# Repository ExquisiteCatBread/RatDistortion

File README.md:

# RatDistortion
Guitar pedal based on Proco RAT

See "Distortion pedal project documentation.pdf"

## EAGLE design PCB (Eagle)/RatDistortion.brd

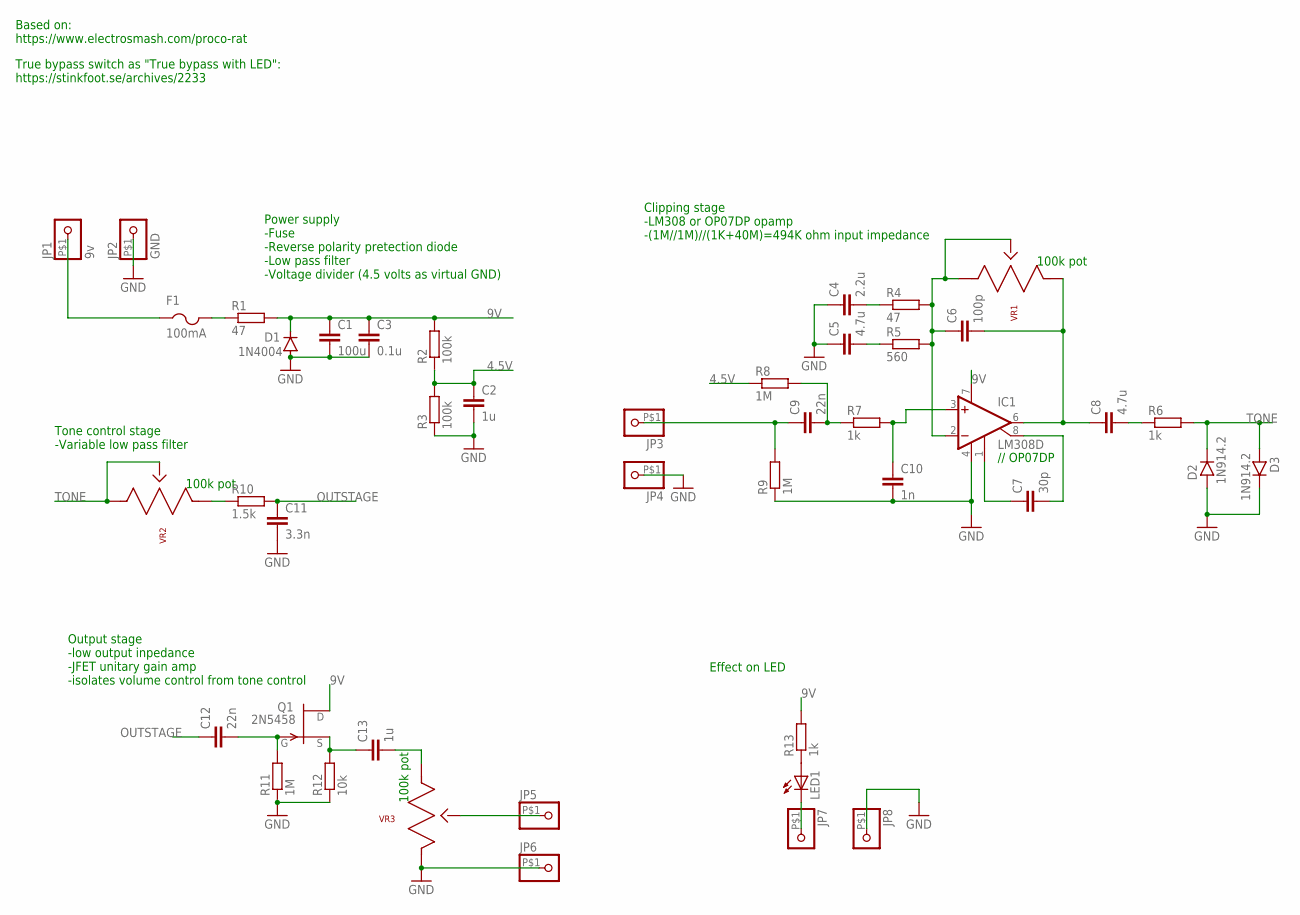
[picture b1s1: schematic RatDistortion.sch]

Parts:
C1: 100u; C1206
C2, C13: 1u; C1206
C3: 0.1u; C0603
C4: 2.2u; C1206
C5, C8: 4.7u; C1206
C6: 100p; C0603
C7: 30p; C0603
C9, C12: 22n; C0603
C10: 1n; C0603
C11: 3.3n; C0603
D1: 1N4004; DO41-10
D2, D3: 1N914.2; DO35-2
F1: 100mA; 1812
IC1: LM308D; SO08
JP1: 9v; 1X1-BIGPOGO
JP2: GND; 1X1-BIGPOGO
JP3, JP4, JP5, JP6, JP7, JP8: PINHD-1X1-BIGPOGO; 1X1-BIGPOGO
LED1: LED3MM
Q1: 2N5458; TO92
R1, R4: 47; R0603
R2, R3: 100k; R0603
R5: 560; R0603
R6, R7, R13: 1k; R0603
R8, R9, R11: 1M; R0603
R10: 1.5k; R0603
R12: 10k; R0603
VR1, VR2, VR3: PTV09A-4225F-B104; PTV09

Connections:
4.5V: C2.1, R2.1, R3.2, R8.1
9V: C1.1, C3.1, D1.C, IC1.7 (V+), Q1.3 (D), R1.2, R2.2, R13.2
GND: C1.2, C2.2, C3.2, C4.1, C5.1, C10.2, C11.2, D1.A, D2.A, D3.C, IC1.4 (V-), JP2.P$1, JP4.P$1, JP6.P$1, JP8.P$1, R3.1, R9.1, R11.1, R12.1, VR3.1
unnamed: F1.2, R1.1
unnamed: F1.1, JP1.P$1
unnamed: C4.2, R4.1
unnamed: C5.2, R5.1
unnamed: C6.1, IC1.2 (-IN), R4.2, R5.2, VR1.2, VR1.3
unnamed: C6.2, C8.1, IC1.6 (OUT), VR1.1
unnamed: C8.2, R6.1
unnamed: C12.2, Q1.1 (G), R11.2
unnamed: C7.1, IC1.1 (CMP1)
unnamed: C7.2, IC1.8 (CMP2)
unnamed: C13.1, Q1.2 (S), R12.2
unnamed: C10.1, IC1.3 (+IN), R7.2
unnamed: C9.2, R7.1, R8.2
unnamed: C9.1, JP3.P$1, R9.2
unnamed: R10.1, VR2.1
unnamed: C13.2, VR3.3
unnamed: LED1.A, R13.1
unnamed: JP5.P$1, VR3.2
unnamed: JP7.P$1, LED1.K (C)
OUTSTAGE: C11.1, C12.1, R10.2
TONE: D2.C, D3.A, R6.2, VR2.2, VR2.3

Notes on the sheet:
Power supply -Fuse -Reverse polarity pretection diode -Low pass filter -Voltage divider (4.5 volts as virtual GND)
100k pot
Clipping stage -LM308 or OP07DP opamp -(1M//1M)//(1K+40M)=494K ohm input impedance
Based on: https://www.electrosmash.com/proco-rat
// OP07DP
Tone control stage -Variable low pass filter
Output stage -low output inpedance -JFET unitary gain amp -isolates volume control from tone control
Effect on LED
True bypass switch as "True bypass with LED": https://stinkfoot.se/archives/2233

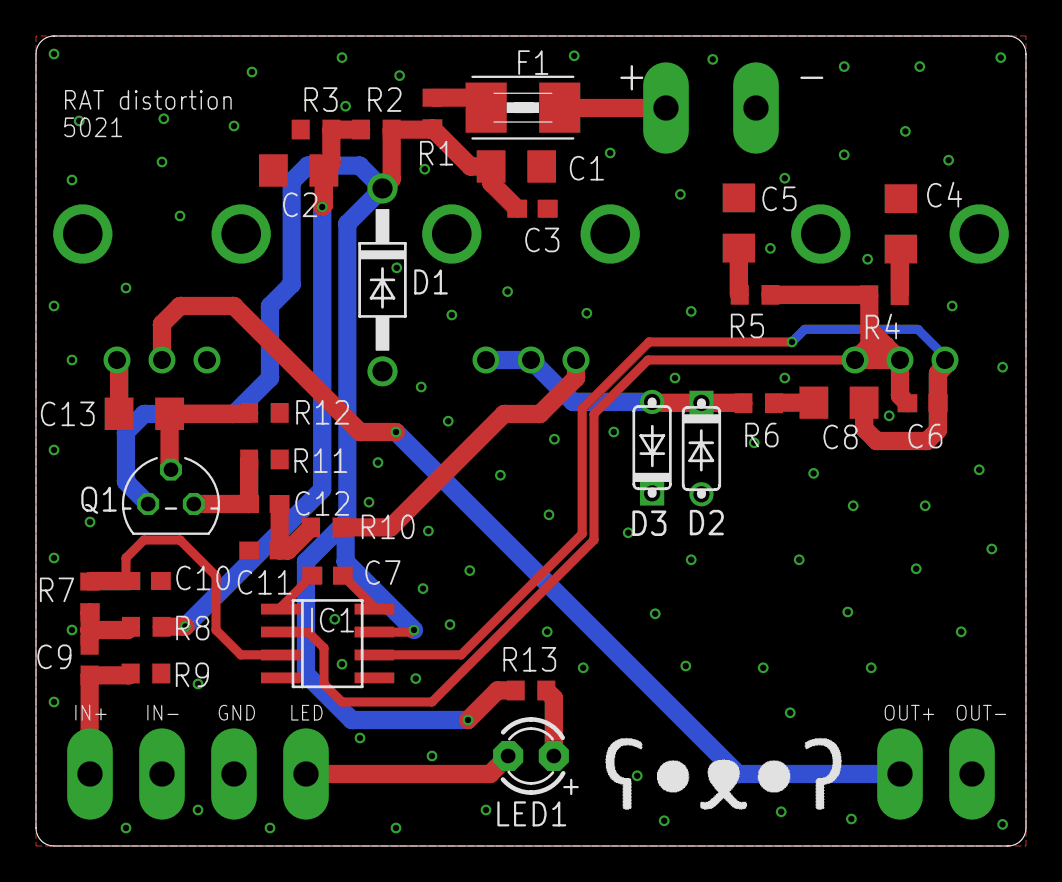
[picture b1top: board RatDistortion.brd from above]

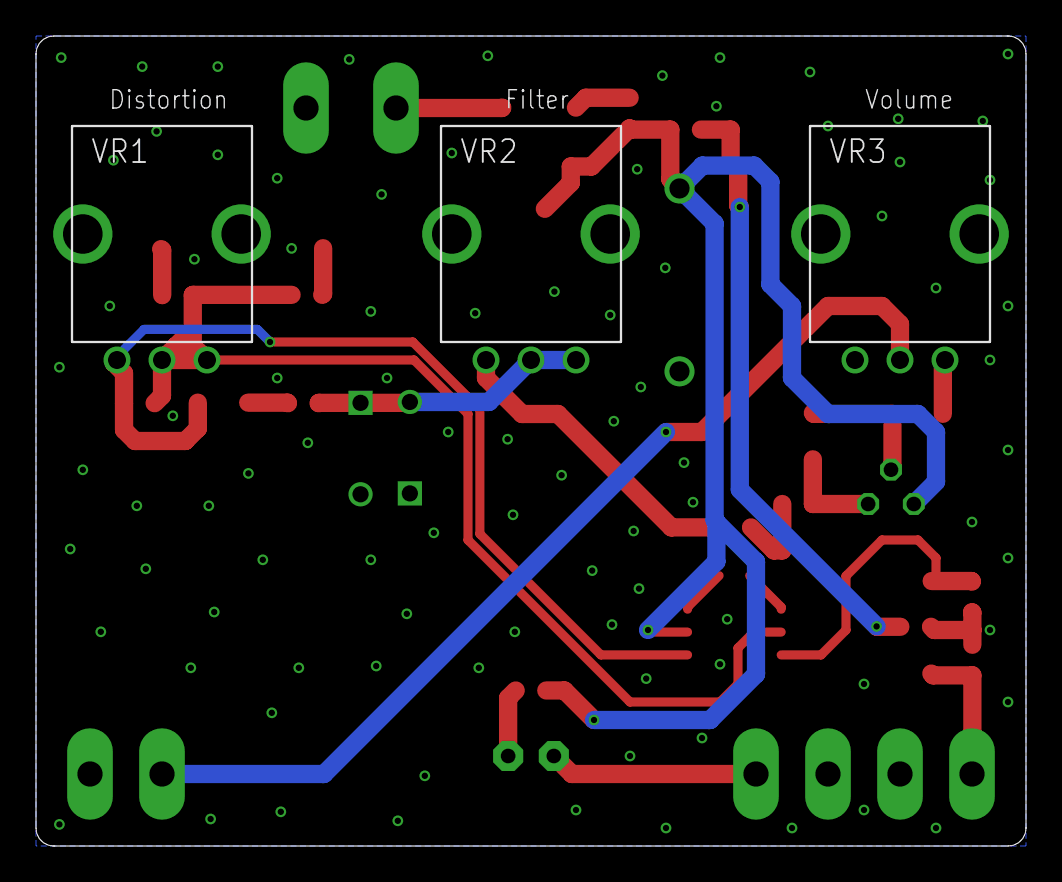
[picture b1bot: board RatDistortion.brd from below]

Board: 2 copper layers, 55.0 x 45.0 mm, 44 parts (4 on the bottom side), 24 nets.

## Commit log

2021-12-10 First
2021-12-11 Update schemetic
2021-12-11 Schemetic and PCB
2021-12-11 Sim net names
2021-12-12 Cleaning, draft doc
    Cleaned folder structure
    Cleaned simulation drawing
    Added documentation draft
2021-12-12 Delete 696103201002.lbr
    Removed unused fuse holder lib
2021-12-12 Create eC_2Layer_PClass6_BaseCopperO18_eCDefault.dru
    Added design rules file
2021-12-14 Updated Eagle files
    JFET 2N5458 (Q1 (was JN1)) in schematic is now correct icon (used default J201 device (same package and pinout)
    Updated PCB to Q1 and made values more readable for documentation (Value will probably not be printed on Silk layer)
2021-12-14 Moved Q1 to own lib Eagle files
2021-12-15 Updated sim (R14 was missing), picture for pcb
2021-12-15 Update PCB
2021-12-15 Updated silk screen error and doc
    PCB as ordered
    Removed LTSpice draft (was in wrong project folder)
2021-12-15 Update Distortion pedal project documentation.pdf
    Document update
2021-12-29 Update doc and simulation
    Made progress on realisation.
    2N5458 JFET seems to be fake and measures as a NPN transistor.
    Made a simulation in the SPICE file to replicate and confirm this.
    Updated doc with temporarily photos and updated price and order list (ordered new JFETS)
    Also added a WIP drill template. (NOT FINAL)
2021-12-30 Updated drill template
2021-12-30 Adjusted drill template after first prototype
2021-12-30 Update doc, added photos
2021-12-30 Picture
2022-01-29 Added test signal pictures
    Added test signal pictures
2022-01-29 First completed version
    Added tests, wire schematic and more photos.
2022-01-29 Update Distortion pedal project documentation.pdf
    Removed errors
2023-04-05 Update README.md
    removed WIP
2023-10-08 Photos
    Photos of laser engraving
